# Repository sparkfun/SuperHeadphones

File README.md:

Super Headphones
========================================

This GitHub Repository contains all the supporting files to host a tutorial that will guide you through how to build your own wireless and/or wired
headphones with ambient microphones. We start with some off-the-shelf headphones
intended for use while lawn mowing, and then hack in some new electronics to allow
wireless (BT), auxiliary 3.5mm TRS input, and stereo ambient microphones. The original
purpose of this project was to make it easy and safe to play loud music with a rock
band in the basement, however, the inclusion of the natural sounds around you into
your listening experience can be useful in many other situations.

[Click here to view the tutorial.](https://docs.sparkfun.com/SuperHeadphones/introduction/)

Repository Contents
-------------------

* **/Documentation** - Datasheets, additional product information
* **/Hardware** - Eagle design files (.brd, .sch)
* **/docs** - Documentation for the github pages version of this hookup guide

License Information
-------------------

This product is _**open source**_!

Please review the LICENSE.md file for license information.

If you have any questions or concerns on licensing, please contact technical support on our [SparkFun forums](https://forum.sparkfun.com/viewforum.php?f=152).

Distributed as-is; no warranty is given.

- Your friends at SparkFun.

_<COLLABORATION CREDIT>_

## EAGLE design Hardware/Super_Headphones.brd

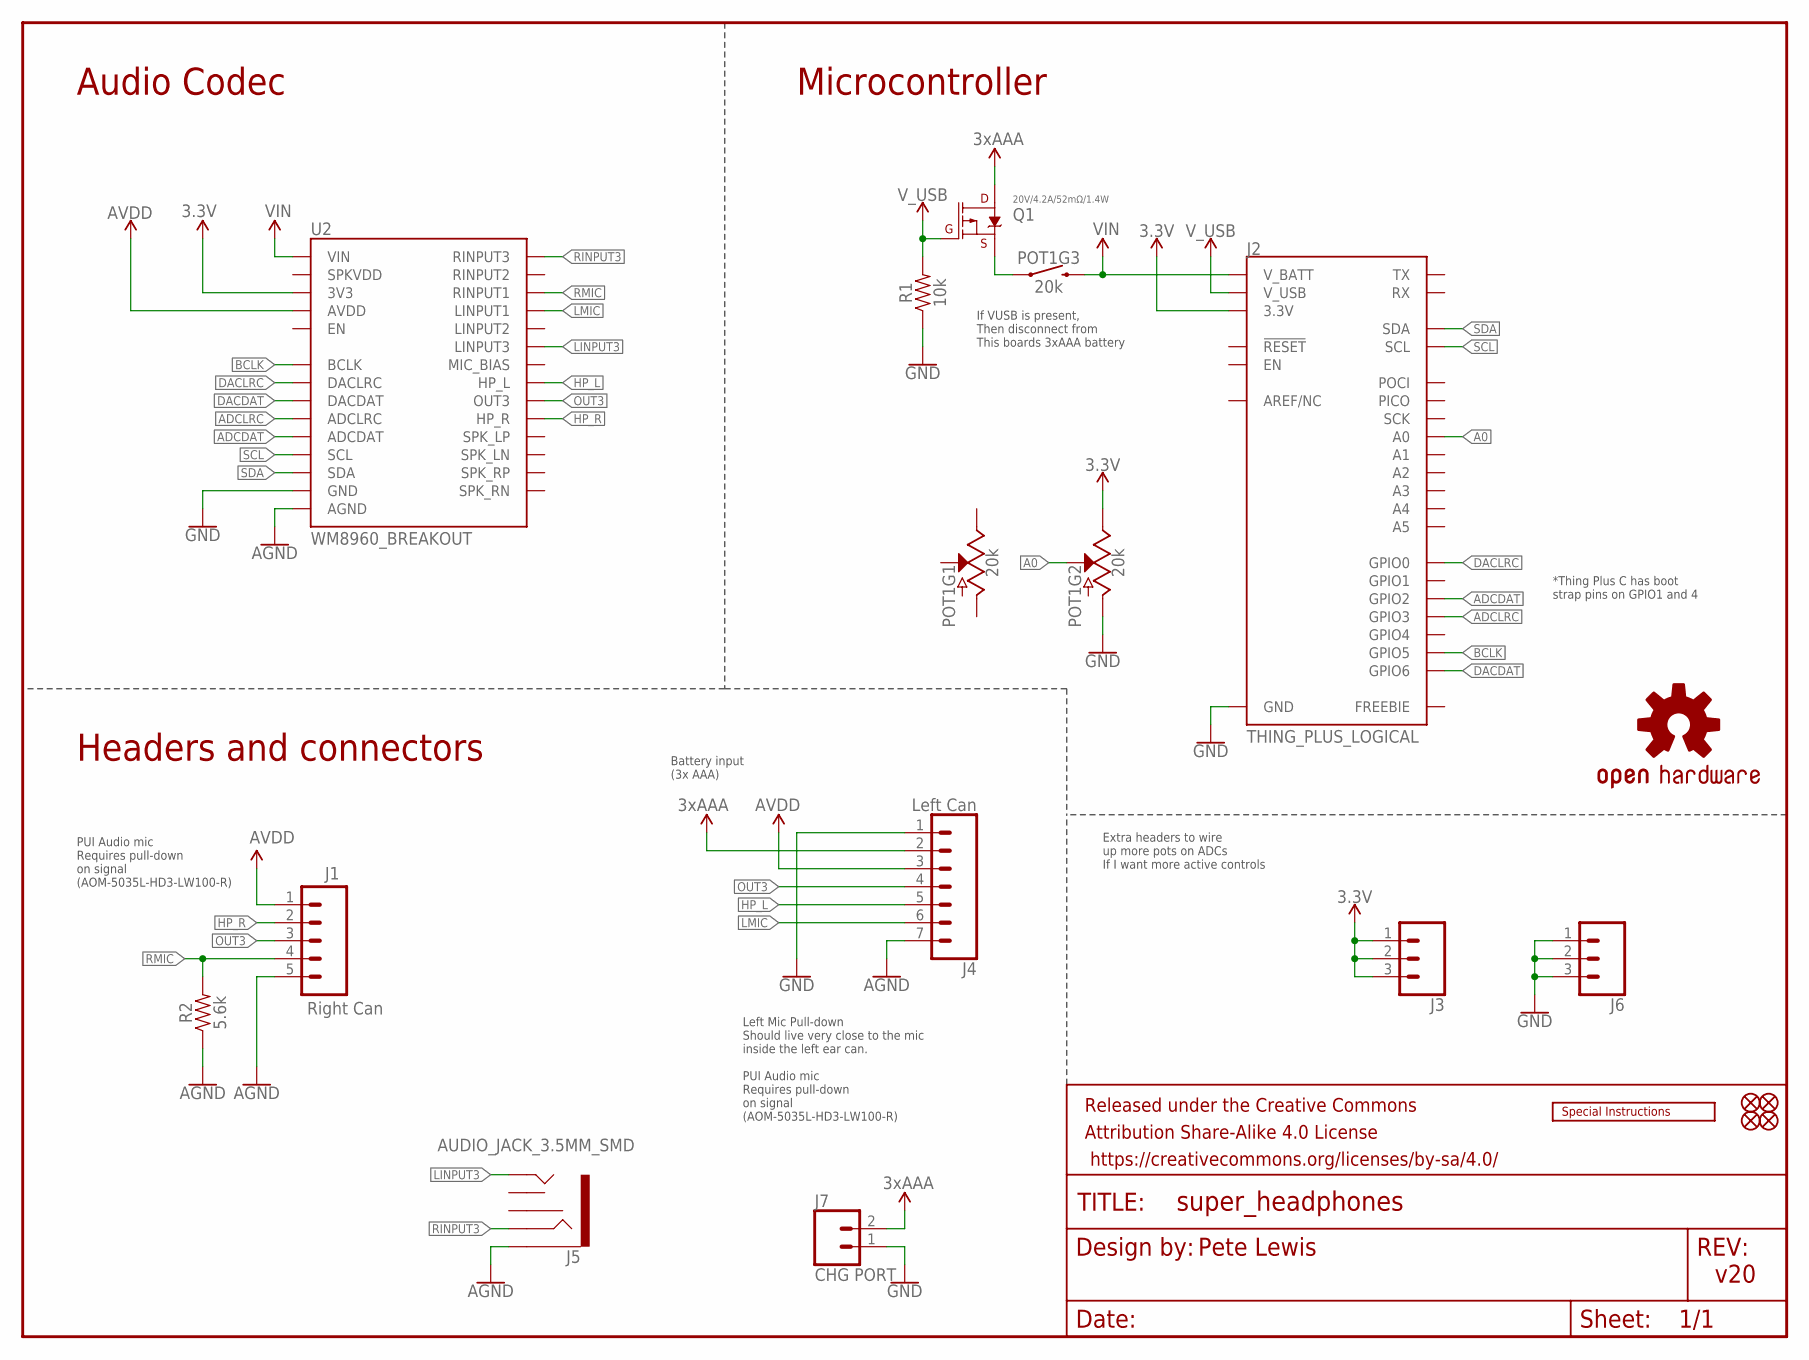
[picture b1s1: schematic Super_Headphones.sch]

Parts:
FD1, FD2, FD3, FD4: FIDUCIALUFIDUCIAL; FIDUCIAL-MICRO
FRAME2: FRAME-LETTER; CREATIVE_COMMONS
J1: Right Can; 1X05_NO_SILK
J2: THING_PLUS_LOGICAL; THING_PLUS
J3, J6: CONN_031X03_NO_SILK; 1X03_NO_SILK
J4: Left Can; 1X07_NO_SILK
J5: AUDIO_JACK_3.5MM_SMD; AUDIO-JACK-3.5MM-SMD
J7: CHG PORT; 1X02_NO_SILK
LOGO4: OSHW-LOGOM; OSHW-LOGO-M
LOGO5: SPECIAL_INSTRUCTIONS-ORDERING; ORDERING_INSTRUCTIONS
POT1: 20k; POT-DUAL-SWITCH-PTH
Q1: 20V/4.2A/52mΩ/1.4W; SOT23-3
R1: 10k; 0603
R2: 5.6k; 0603
U2: WM8960_BREAKOUT

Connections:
3.3V: J2.27 (3.3V), J3.1, J3.2, J3.3, POT1.B3 (E), U2.3V3
3XAAA: J4.2, J7.2, Q1.3 (D)
A0: J2.24 (A0), POT1.B2 (S)
ADCDAT: J2.7 (GPIO2), U2.ADCDAT
ADCLRC: J2.6 (GPIO3), U2.ADCLRC
AGND: J1.5, J4.7, J5.SLEEVE, R2.1, U2.GND1 (AGND)
AVDD: J1.1, J4.3, U2.AVDD
BCLK: J2.4 (GPIO5), U2.BCLK
DACDAT: J2.3 (GPIO6), U2.DACDAT
DACLRC: J2.9 (GPIO0), U2.DACLRC
GND: J2.25 (GND), J4.1, J6.1, J6.2, J6.3, J7.1, POT1.B1 (A), R1.1, U2.GND2 (GND), U2.GND3 (GND), U2.GND4 (GND), U2.GND5 (GND), U2.GND6 (GND)
HP_L: J4.5, U2.HP_L
HP_R: J1.2, U2.HP_R
LINPUT3: J5.TIP, U2.LINPUT3
LMIC: J4.6, U2.LINPUT1
unnamed: POT1.SW1 (1), Q1.2 (S)
OUT3: J1.3, J4.4, U2.OUT3
RINPUT3: J5.RING, U2.RINPUT3
RMIC: J1.4, R2.2, U2.RINPUT1
SCL: J2.2 (SCL), U2.SCL
SDA: J2.1 (SDA), U2.SDA
VIN: J2.12 (V_BATT), POT1.SW2 (2), U2.VIN
V_USB: J2.10 (V_USB), Q1.1 (G), R1.2

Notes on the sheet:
Pete Lewis
Audio Codec
v20
*Thing Plus C has boot strap pins on GPIO1 and 4
Battery input (3x AAA)
If VUSB is present, Then disconnect from This boards 3xAAA battery
Extra headers to wire up more pots on ADCs If I want more active controls
PUI Audio mic Requires pull-down on signal (AOM-5035L-HD3-LW100-R)
Left Mic Pull-down Should live very close to the mic inside the left ear can. PUI Audio mic Requires pull-down on signal (AOM-5035L-HD3-LW100-R)
Microcontroller
Headers and connectors

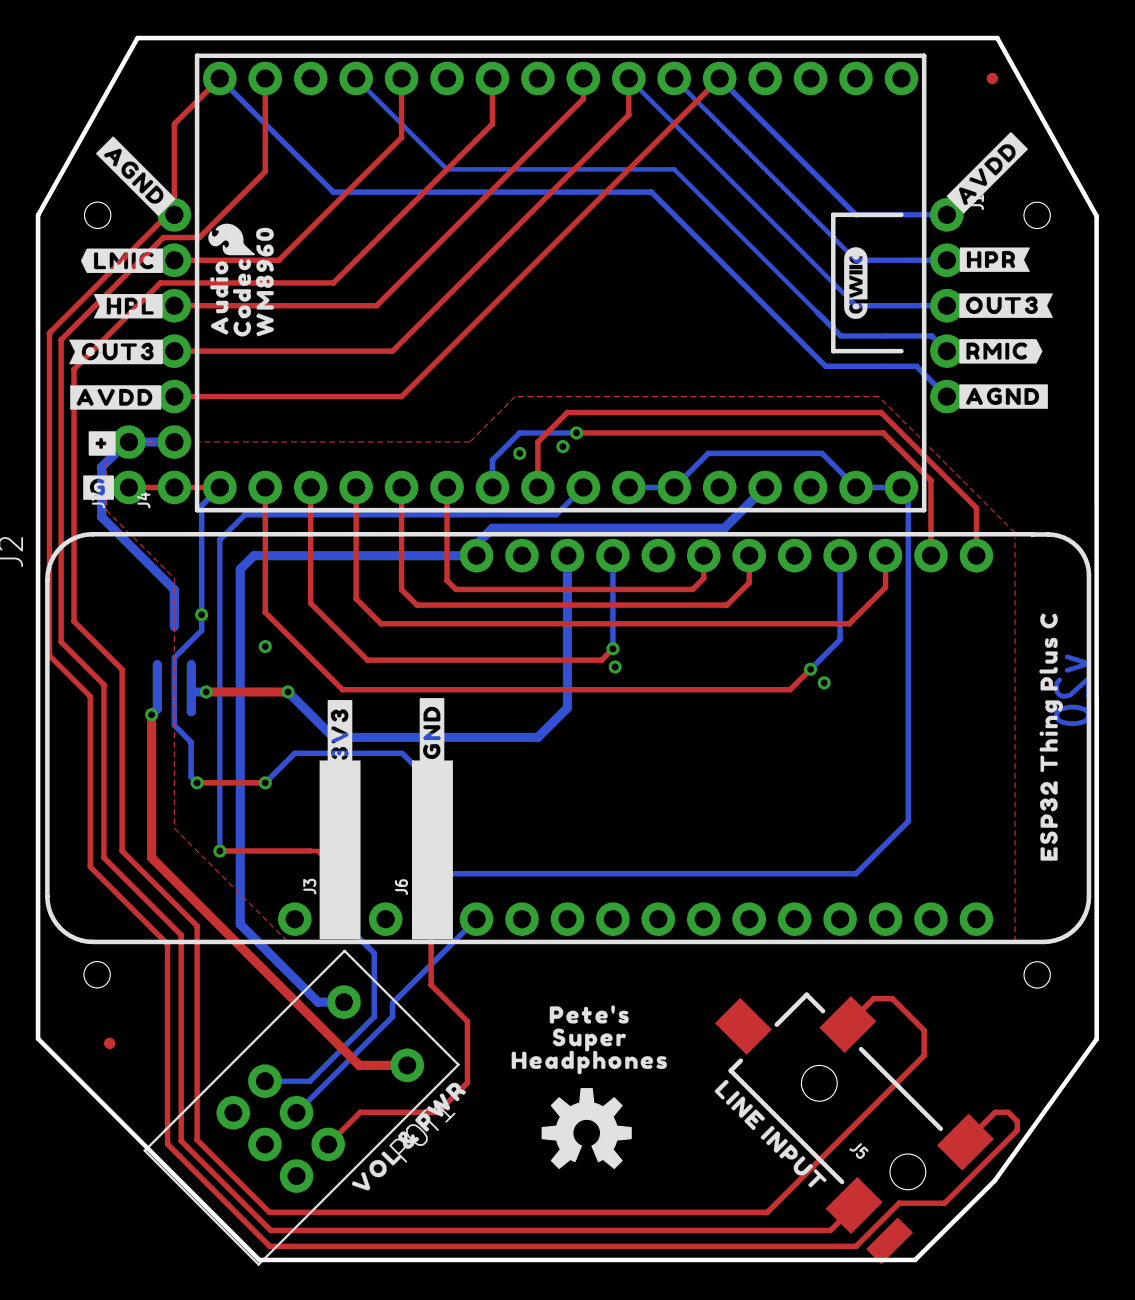
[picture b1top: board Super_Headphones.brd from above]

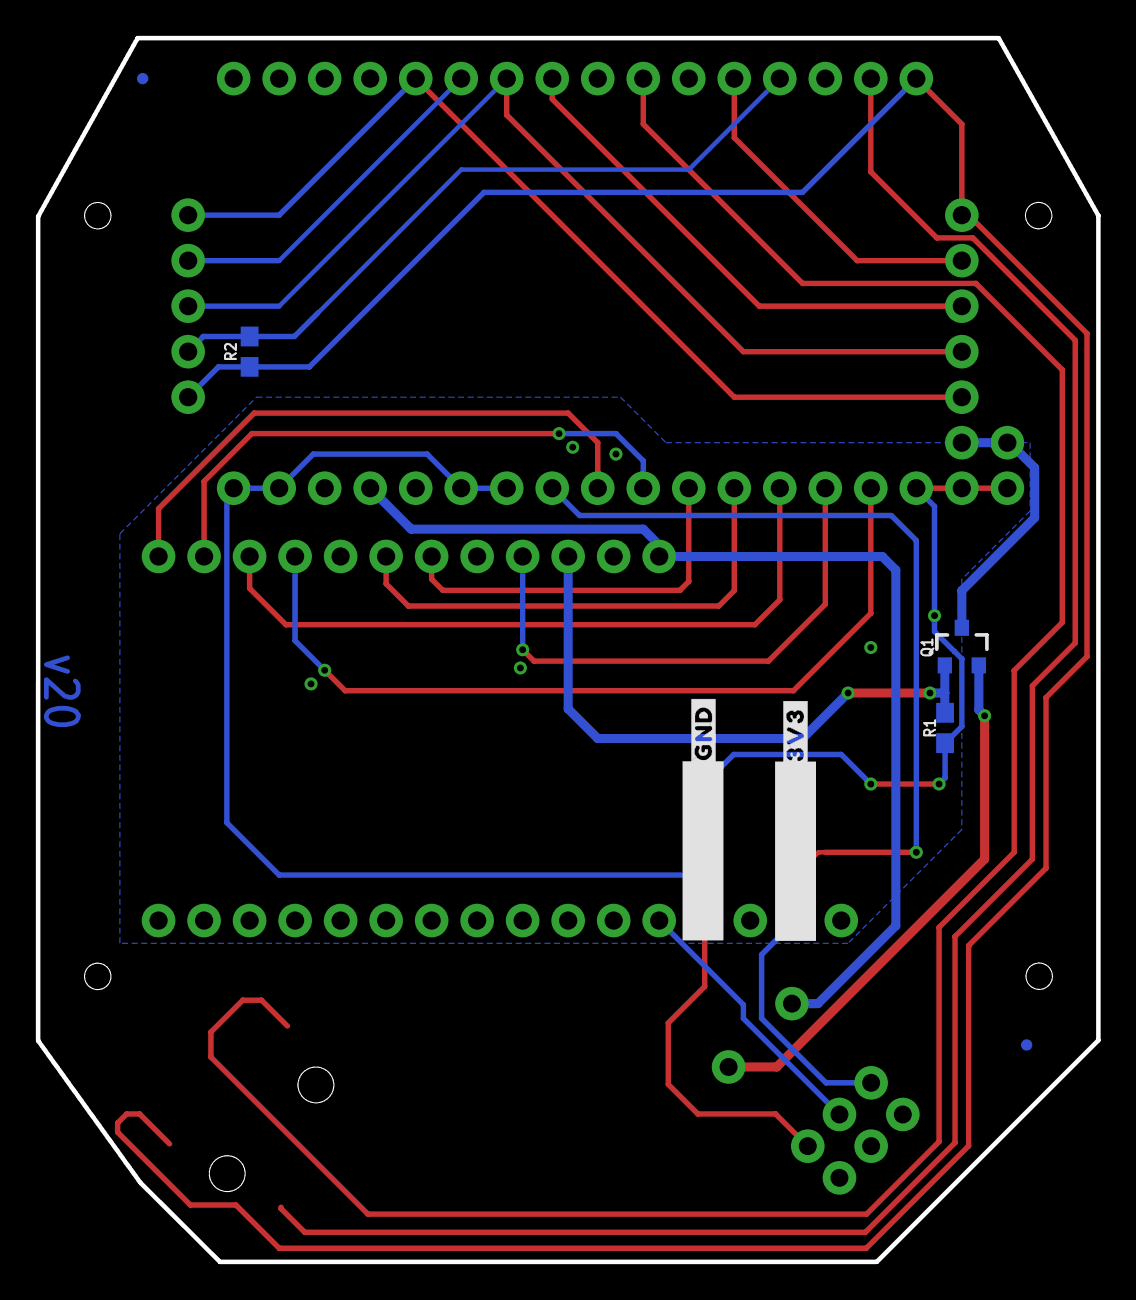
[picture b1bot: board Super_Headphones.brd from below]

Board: 4 copper layers, 59.2 x 68.3 mm, 41 parts (7 on the bottom side), 23 nets.

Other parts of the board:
U$2, U$17: #AGND#0
U$5: #LMIC#503
U$6: #HPL#504
U$7: #OUT3#505
U$8, U$13: #AVDD#505
U$9: ###507
U$10: #HPR#509
U$11: #OUT3#510
U$14: #RMIC#510
U$15: LINE_INPUT512
U$16: VOL_#_PWR513
U$18: #G#514
U$19: PETE#S516
U$20: SUPER517
U$21: HEADPHONES518
U$22, U$23: #GND#502
U$24, U$25: #3V3#519
U$26: ESP32_THING_PLUS_C519

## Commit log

2023-08-03 fresh copies of stuff from docs-github_page
2023-08-03 adjusting repo name and stuff
2023-08-03 readme file name typo
2023-08-04 More naming and URL stuff
2023-08-23 testing images
2023-08-23 intro almost there
    -added hardware files
    -added arduino code files
    -added microphone datasheet
2023-08-23 intro update
2023-09-06 intro and hw overview work
2023-09-08 intro and hw overview pretty much done.
    -new wiring diagram!
    -also did some image size cleanup.
2023-09-11 notes on mic pull-down resistors
2023-09-11 Arduino code section WIP
2023-09-11 Almost done
2023-09-12 filled in some resources
    -added measures to design files
    -created dimensions pdf and png
    -filled in resources links
    -added app note about mic specs
2023-09-12 More resource links
2023-09-12 more history added and assembly instructions
2023-09-12 more parts links
2023-09-12 update readme - the right readme this time
2023-09-18 More info about arduino code
    -added some instructions to connect over BT with your PC or cell.
    -some adjustment of images.
    -renames microphone testing section to be more accurate.
2023-09-19 Fix minor typos, grammar, and format =)
2023-09-19 more minor typos
2023-09-19 re-arranging resources
    -added code as zip with link at top
    -added dxf of dimensions
    -re-arranged to have general stuff on top of list
2023-09-19 new GIF with arrows and text
2023-09-19 removing left over artifact from template - software_setup.md
2023-09-19 updating arduino code link
2023-09-19 arduino code display file name update
2023-09-19 forgot file extension ".ino"
2023-09-19 Minor Aesthetic Updates and Fixing Single Page View
2023-11-14 Remove "Hide" from Style
    - Remove the "hide" from the style to ensure that the images/tutorials show up when printing
2023-12-08 Link IEEE Article
2023-12-08 Deployed 45a7070 with MkDocs version: 1.5.3
2023-12-30 c6 support
    -note, I already brought some of this back to esp32 thing plus C
    -added pin defines for I2S (note, this also uses a differente ADC pin (2). And it sets up I2C on other GPIO (not qwiic connector) for easier soldering access in the headphone can.
    -added Bluetooth macro to more easily turn this feature on and off
    -added VROI and setVSEL controls (note, not tested yet, but added into a branch of the codec library)
    -
2024-02-16 Remove cache
2024-02-16 Add 360 photos
2024-02-16 Include javascript
    Add javascript file
    Enables script to run
2024-02-16 Add 360 view
    Enables javascript to provide 360 project view
2024-02-16 360 product view
    Styling for 360 view
    - image is hard coded to take up 85% of element, with a max width of 250px
2024-02-17 Resize images
    Reduced resolution to save on memory and speed up load time
2024-10-29 Add cookies
2024-10-29 Deployed 5cbeca6 with MkDocs version: 1.6.1
2025-02-19 Fix broken links
2025-02-19 Deployed a564f96 with MkDocs version: 1.6.1
2025-07-07 ESP32-C6 support
2026-06-03 Deployed 742962c with MkDocs version: 1.6.1

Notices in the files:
parts and their libraries:
SparkFun-Resistors: Licensing: Creative Commons ShareAlike 4.0 International - https://creativecommons.org/licenses/by-sa/4.0
SparkFun-Aesthetics: Released under the Creative Commons Attribution Share-Alike 4.0 License
SparkFun-Aesthetics: https://creativecommons.org/licenses/by-sa/4.0
